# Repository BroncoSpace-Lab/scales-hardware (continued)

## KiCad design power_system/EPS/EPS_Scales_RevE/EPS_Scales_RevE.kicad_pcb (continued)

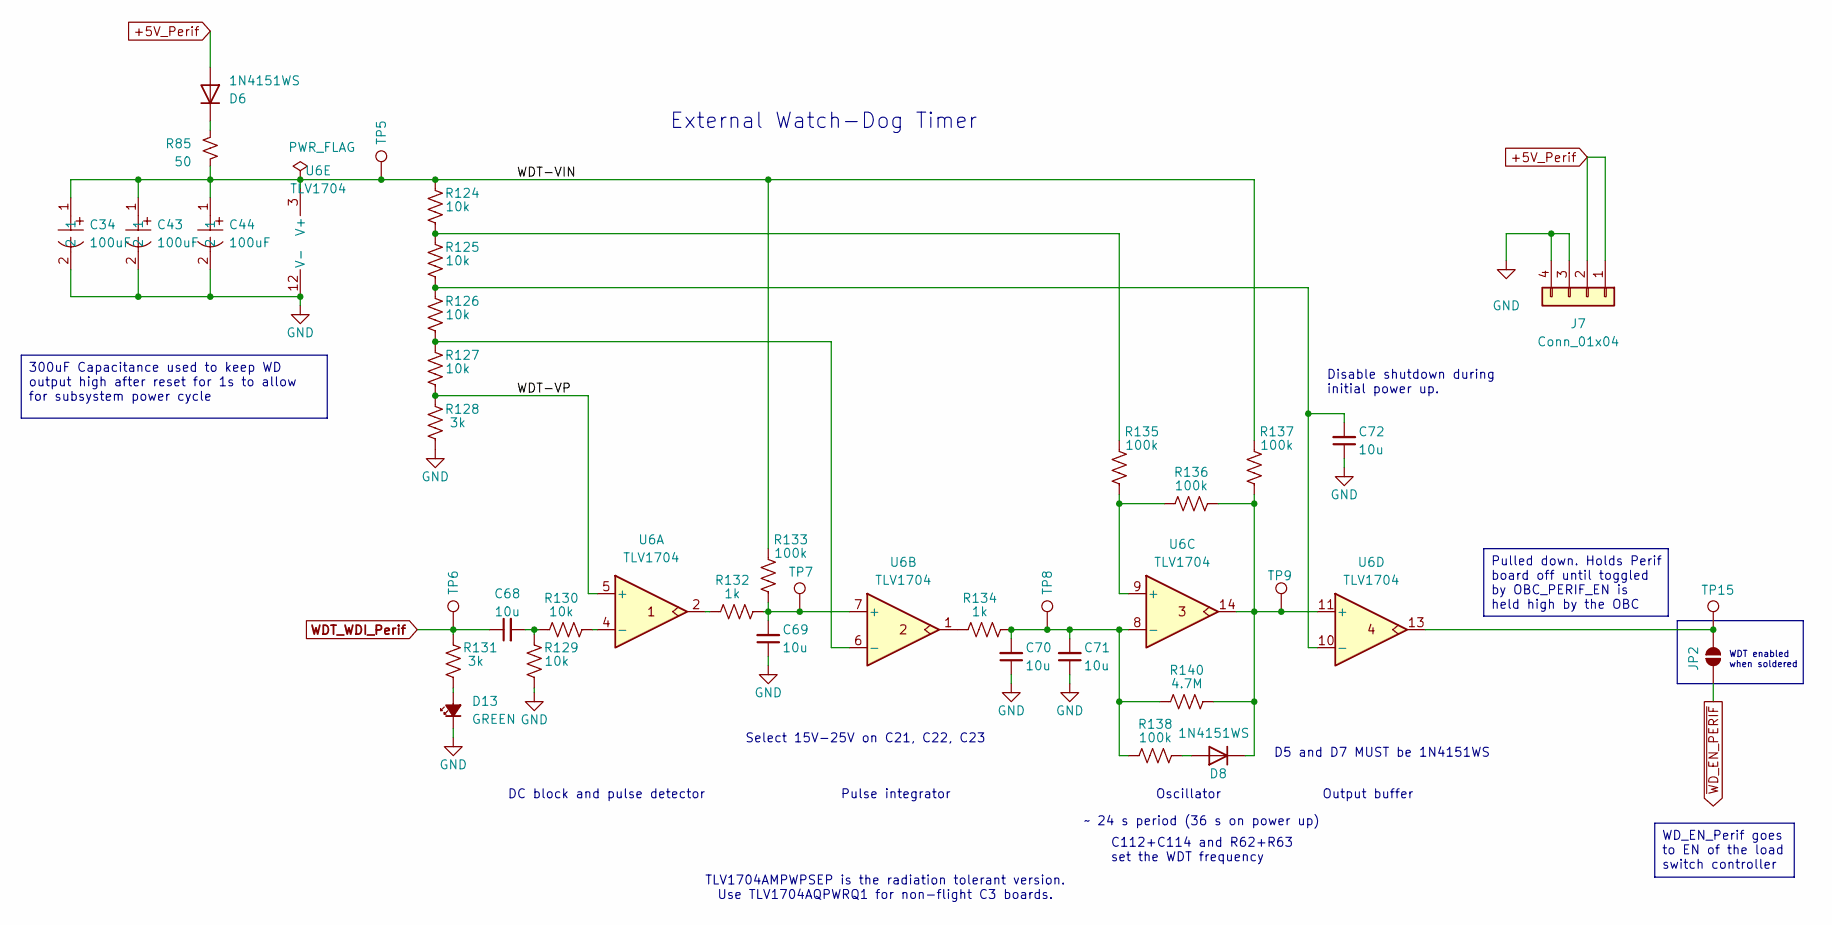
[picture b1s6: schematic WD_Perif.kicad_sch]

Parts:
C34, C43, C44: 100uF; CAP-SMD_L7.3-W6.1_TCN4227M025R0100; LCSC Part C2158793
C68, C69, C70, C71, C72: 10u; C0402; LCSC 194427
D6, D8: 1N4151WS; SOD2512X116N; MPN 1N4151WS-E3-08; LCSC C2979762
D13: GREEN; LED_0603_1608Metric; MPN 150060GS75000; LCSC C965799
J7: Conn_01x04; PinSocket_1x04_P2.54mm_Vertical
JP2: SolderJumper_2_Open; SolderJumper-2_P1.3mm_Open_RoundedPad1.0x1.5mm
R85: 50; R_1206_3216Metric; MPN ESR18EZPF10R0; LCSC C17903
R124, R125, R126, R127, R129, R130: 10k; R0402; LCSC C25531
R128, R131: 3k; R0402; LCSC C2909355
R132, R134: 1k; R0402; LCSC C106235
R133, R135, R136, R137, R138: 100k; R0402; LCSC C269673
R140: 4.7M; R0402; LCSC C474132
TP5, TP6, TP7, TP8, TP9, TP15: TestPoint; TestPoint_Pad_1.0x1.0mm
U6: TLV1704; TSSOP-14_4.4x5mm_P0.65mm; MPN TLV1704AQPWRQ1; LCSC C181596

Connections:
+5V_Perif: D6.2 (A), J7.1, J7.2; also elsewhere on the board
/Perif_Subsystem/WD_Perif/WDT-VIN: C34.1, C43.1, C44.1, R85.2, R124.2, R133.1, R137.1, TP5.1, U6.3 (V+)
/Perif_Subsystem/WD_Perif/WDT-VP: R127.1, R128.2, U6.5 (+)
GND: C34.2, C43.2, C44.2, C69.1, C70.1, C71.1, C72.1, D13.1 (K), J7.3, J7.4, R128.1, R129.1, U6.12 (V-); also elsewhere on the board
unnamed: C68.2, R129.2, R130.2
unnamed: D6.1 (C), R85.1
unnamed: D8.2 (A), R138.2
unnamed: D8.1 (C), R136.2, R137.2, R140.2, TP9.1, U6.11 (+), U6.14
unnamed: D13.2 (A), R131.1
unnamed: JP2.1 (A), TP15.1, U6.13
unnamed: R124.1, R125.2, R135.1
unnamed: R132.2, U6.2
unnamed: R134.2, U6.1
unnamed: R130.1, U6.4 (-)
unnamed: C69.2, R132.1, R133.2, TP7.1, U6.7 (+)
unnamed: R126.1, R127.2, U6.6 (-)
unnamed: R135.2, R136.1, U6.9 (+)
unnamed: C70.2, C71.2, R134.1, R138.1, R140.1, TP8.1, U6.8 (-)
unnamed: C72.2, R125.1, R126.2, U6.10 (-)
WDT_WDI_Perif: C68.1, R131.2, TP6.1; also elsewhere on the board
~WD_EN_PERIF: JP2.2 (B); also elsewhere on the board

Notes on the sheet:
External Watch-Dog Timer
Output buffer
TLV1704AMPWPSEP is the radiation tolerant version. Use TLV1704AQPWRQ1 for non-flight C3 boards.
~ 24 s period (36 s on power up)
Disable shutdown during initial power up.
DC block and pulse detector
WDT enabled when soldered
D5 and D7 MUST be 1N4151WS
Pulse integrator
Oscillator
C112+C114 and R62+R63 set the WDT frequency
Select 15V-25V on C21, C22, C23
WD_EN_Perif goes to EN of the load switch controller
300uF Capacitance used to keep WD output high after reset for 1s to allow for subsystem power cycle
Pulled down. Holds Perif board off until toggled by OBC_PERIF_EN is held high by the OBC

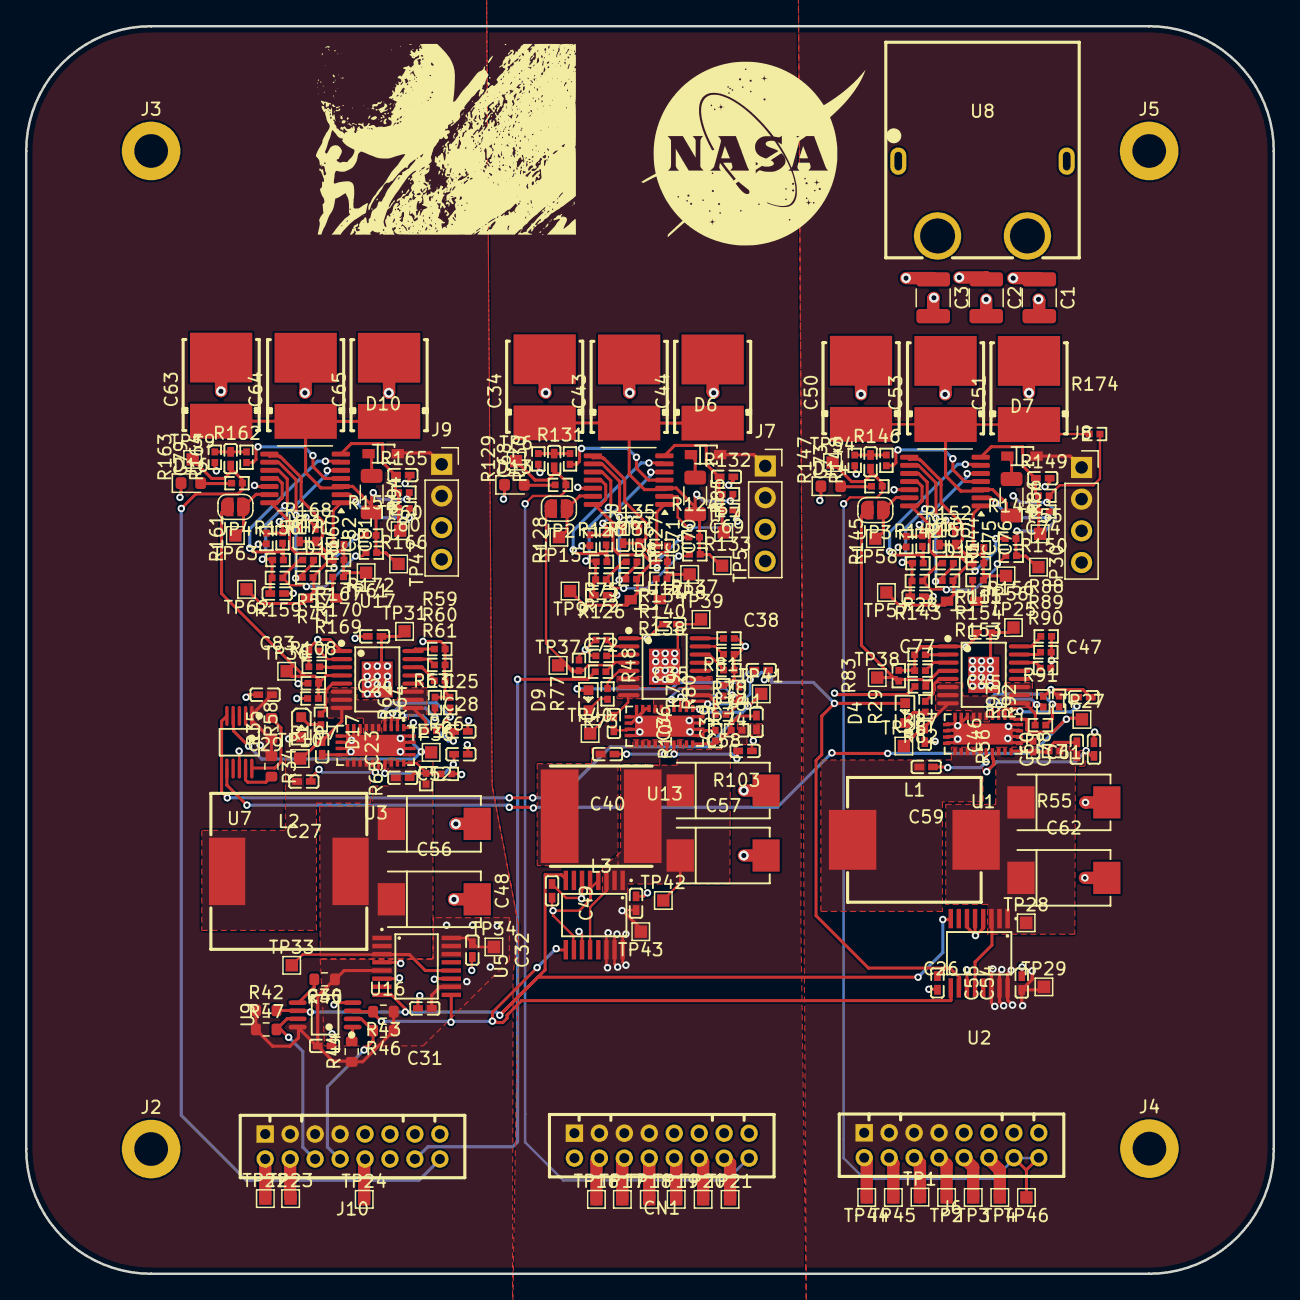
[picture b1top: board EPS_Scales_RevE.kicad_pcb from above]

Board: 4 copper layers, 100.0 x 100.0 mm, 253 parts (0 on the bottom side), 139 nets.

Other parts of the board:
C1, C2, C3: 10u; C_1210_3225Metric
J2, J3, J4, J5: Conn_01x01_Socket; MountingHole_2.7mm_M2.5_DIN965_Pad
U8: XT60PW-F_C428722; TH_2P-XT60PW-F

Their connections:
+V_Batt: C1.1, C2.1, C3.1, U8.3 (+); also elsewhere on the board
GND: C1.2, C2.2, C3.2, J2.1, J3.1, J4.1, J5.1, U8.1, U8.2, U8.4 (-); also elsewhere on the board

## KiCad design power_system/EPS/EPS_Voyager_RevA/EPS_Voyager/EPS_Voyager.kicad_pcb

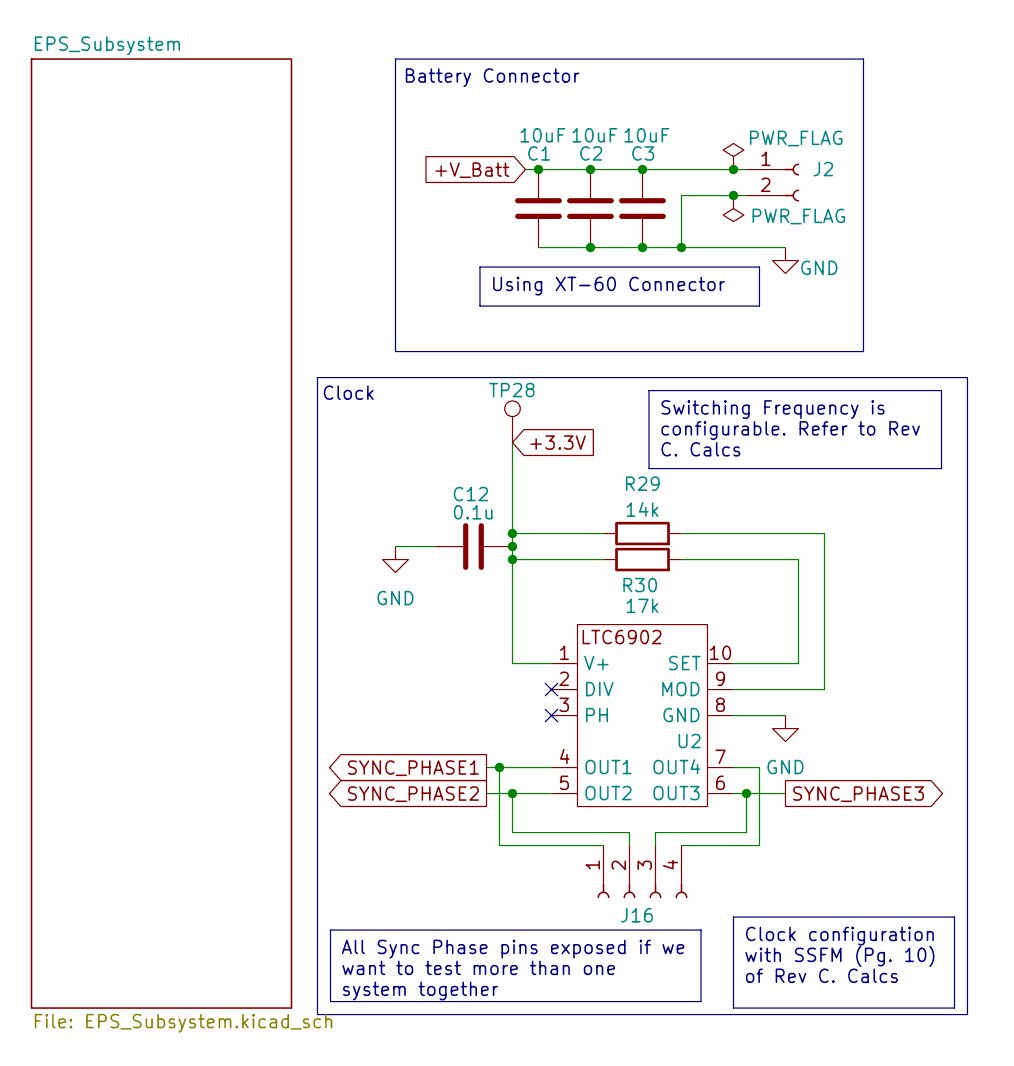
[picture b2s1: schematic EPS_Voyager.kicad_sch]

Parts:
C1, C2, C3: 10uF; C_1210_3225Metric
C12: 0.1u; C_1210_3225Metric
J2: Input Power; AMASS_XT60PW-F_1x02_P7.20mm_Horizontal
J16: Conn_01x04_Socket; PinSocket_1x04_P2.54mm_Vertical
R29: 14k
R30: 17k
TP28: TestPoint; TestPoint_Pad_1.0x1.0mm
U2: LTC6902

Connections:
+3.3V: C12.2, R29.1, R30.1, TP28.1, U2.1 (V+); also elsewhere on the board
+V_Batt: C1.1, C2.1, C3.1, J2.1; also elsewhere on the board
GND: C1.2, C2.2, C3.2, C12.1, J2.2, U2.8 (GND); also elsewhere on the board
unnamed 13: R29.2, U2.9 (MOD); also elsewhere on the board
unnamed 14: R30.2, U2.10 (SET); also elsewhere on the board
unnamed: J16.4, U2.7 (OUT4)
SYNC_PHASE1: J16.1, U2.4 (OUT1)
SYNC_PHASE2: J16.2, U2.5 (OUT2)
SYNC_PHASE3: J16.3, U2.6 (OUT3)

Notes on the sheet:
Clock
Battery Connector
Switching Frequency is configurable. Refer to Rev C. Calcs
Clock configuration with SSFM (Pg. 10) of Rev C. Calcs
Using XT-60 Connector
All Sync Phase pins exposed if we want to test more than one system together

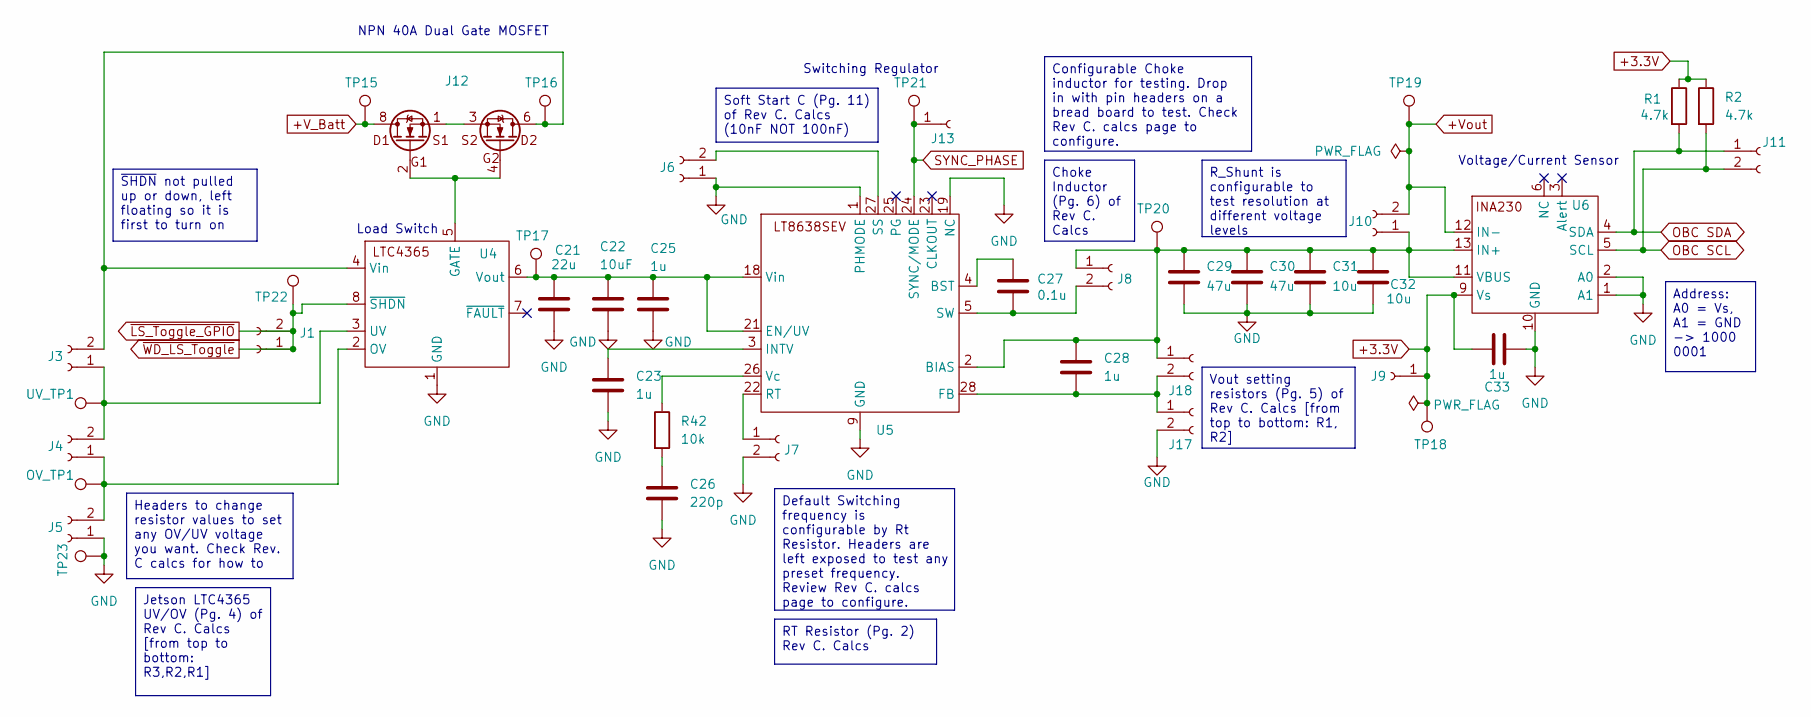
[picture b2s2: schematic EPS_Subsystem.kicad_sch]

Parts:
C21: 22u; C_1210_3225Metric
C22: 10uF; C_1210_3225Metric
C23, C25, C28, C33: 1u; C_1210_3225Metric
C26: 220p; C_1210_3225Metric
C27: 0.1u; C_1210_3225Metric
C29, C30: 47u; C_1210_3225Metric
C31, C32: 10u; C_1210_3225Metric
J1, J3, J4, J5, J6, J7, J8, J10, J11, J17, J18: Conn_01x02_Socket; PinSocket_1x02_P2.54mm_Vertical
J9, J13: Conn_01x01_Socket; PinSocket_1x01_P2.54mm_Vertical
J12: SISB46DN-T1-GE3
OV_TP1: TestPoint; TestPoint_Pad_1.0x1.0mm
R1, R2: 4.7k; R_0603_1608Metric
R42: 10k; R_0603_1608Metric
TP15, TP16, TP17, TP18, TP19, TP20, TP21, TP22, TP23: TestPoint; TestPoint_Pad_1.0x1.0mm
U4: LTC4365
U5: LT8638SEVPBF
U6: INA230; INA230AIRGTT
UV_TP1: TestPoint; TestPoint_Pad_1.0x1.0mm

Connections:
+3.3V: C33.2, J9.1, R1.1, R2.1, TP18.1, U6.9 (Vs); also elsewhere on the board
+V_Batt: J12.7, J12.8, TP15.1; also elsewhere on the board
+Vout: J10.2, TP19.1, U6.12 (IN-)
GND: C21.2, C22.2, C23.2, C25.2, C26.2, C29.2, C30.2, C31.2, C32.2, C33.1, J5.1, J6.1, J7.2, J17.2, TP23.1, U4.1 (GND), U5.1 (PHMODE), U5.9 (GND), U5.19 (NC), U6.1 (A1), U6.2 (A0), U6.10 (GND); also elsewhere on the board
unnamed: C26.1, R42.2
unnamed: J3.1, J4.2, U4.3 (UV), UV_TP1.1
unnamed: J3.2, J12.5, J12.6, TP16.1, U4.4 (Vin)
unnamed: J4.1, J5.2, OV_TP1.1, U4.2 (OV)
unnamed: J6.2, U5.27 (SS)
unnamed: J7.1, U5.22 (RT)
unnamed: C27.2, J8.2, U5.5 (SW)
unnamed: C28.1, C29.1, C30.1, C31.1, C32.1, J8.1, J10.1, J18.1, TP20.1, U5.2 (BIAS), U6.11 (VBUS), U6.13 (IN+)
unnamed: J12.1, J12.3
unnamed: C28.2, J17.1, J18.2, U5.28 (FB)
unnamed: J12.2, J12.4, U4.5 (GATE)
unnamed: C21.1, C22.1, C25.1, TP17.1, U4.6 (Vout), U5.18 (Vin), U5.21 (EN/UV)
unnamed: C27.1, U5.4 (BST)
unnamed: C23.1, U5.3 (INTV)
unnamed: R42.1, U5.26 (Vc)
OBC SCL: J11.2, R2.2, U6.5 (SCL)
OBC SDA: J11.1, R1.2, U6.4 (SDA)
SYNC_PHASE: J13.1, TP21.1, U5.24 (SYNC/MODE)
~LS_Toggle_GPIO: J1.1, J1.2, TP22.1, U4.8 (~SHDN)

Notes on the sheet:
Switching Regulator
NPN 40A Dual Gate MOSFET
Voltage/Current Sensor
Load Switch
RT Resistor (Pg. 2) Rev C. Calcs
Soft Start C (Pg. 11) of Rev C. Calcs (10nF NOT 100nF)
Headers to change resistor values to set any OV/UV voltage you want. Check Rev. C calcs for how to
R_Shunt is configurable to test resolution at different voltage levels
Configurable Choke inductor for testing. Drop in with pin headers on a bread board to test. Check Rev C. calcs page to configure.
Address: A0 = Vs, A1 = GND -> 1000 0001
Vout setting resistors (Pg. 5) of Rev C. Calcs [from top to bottom: R1, R2]
Choke Inductor (Pg. 6) of Rev C. Calcs
Jetson LTC4365 UV/OV (Pg. 4) of Rev C. Calcs [from top to bottom: R3,R2,R1]
~{SHDN} not pulled up or down, left floating so it is first to turn on
Default Switching frequency is configurable by Rt Resistor. Headers are left exposed to test any preset frequency. Review Rev C. calcs page to configure.

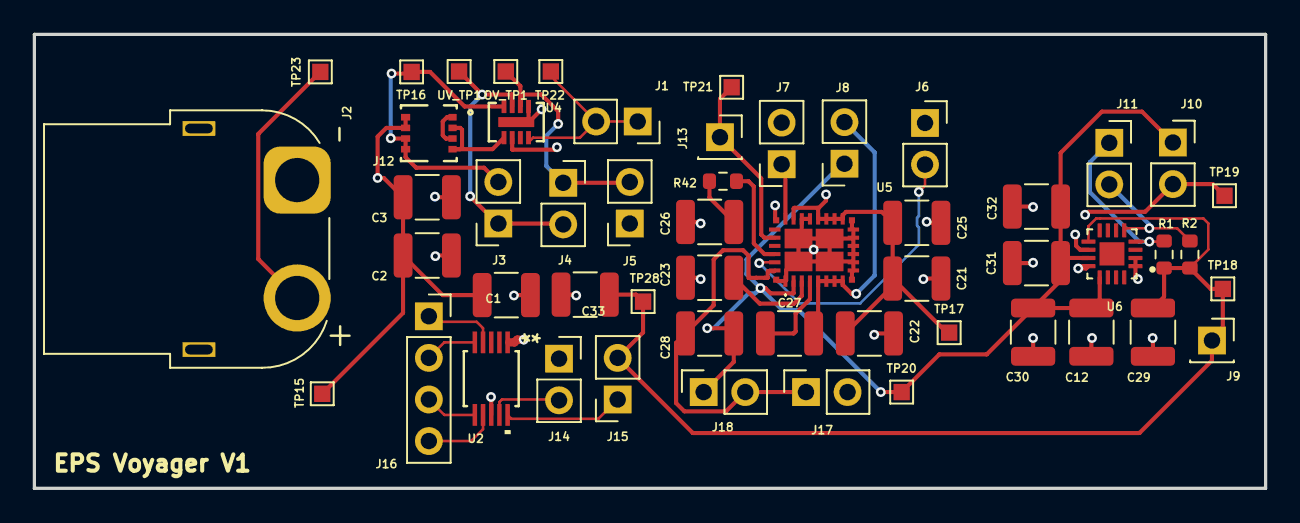
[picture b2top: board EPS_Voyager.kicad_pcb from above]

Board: 4 copper layers, 75.2 x 27.7 mm, 53 parts (0 on the bottom side), 29 nets.

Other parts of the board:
J14, J15: Conn_01x02_Socket; PinSocket_1x02_P2.54mm_Vertical

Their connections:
+3.3V: J14.1, J15.2; also elsewhere on the board
unnamed 13: J14.2; also elsewhere on the board
unnamed 14: J15.1; also elsewhere on the board

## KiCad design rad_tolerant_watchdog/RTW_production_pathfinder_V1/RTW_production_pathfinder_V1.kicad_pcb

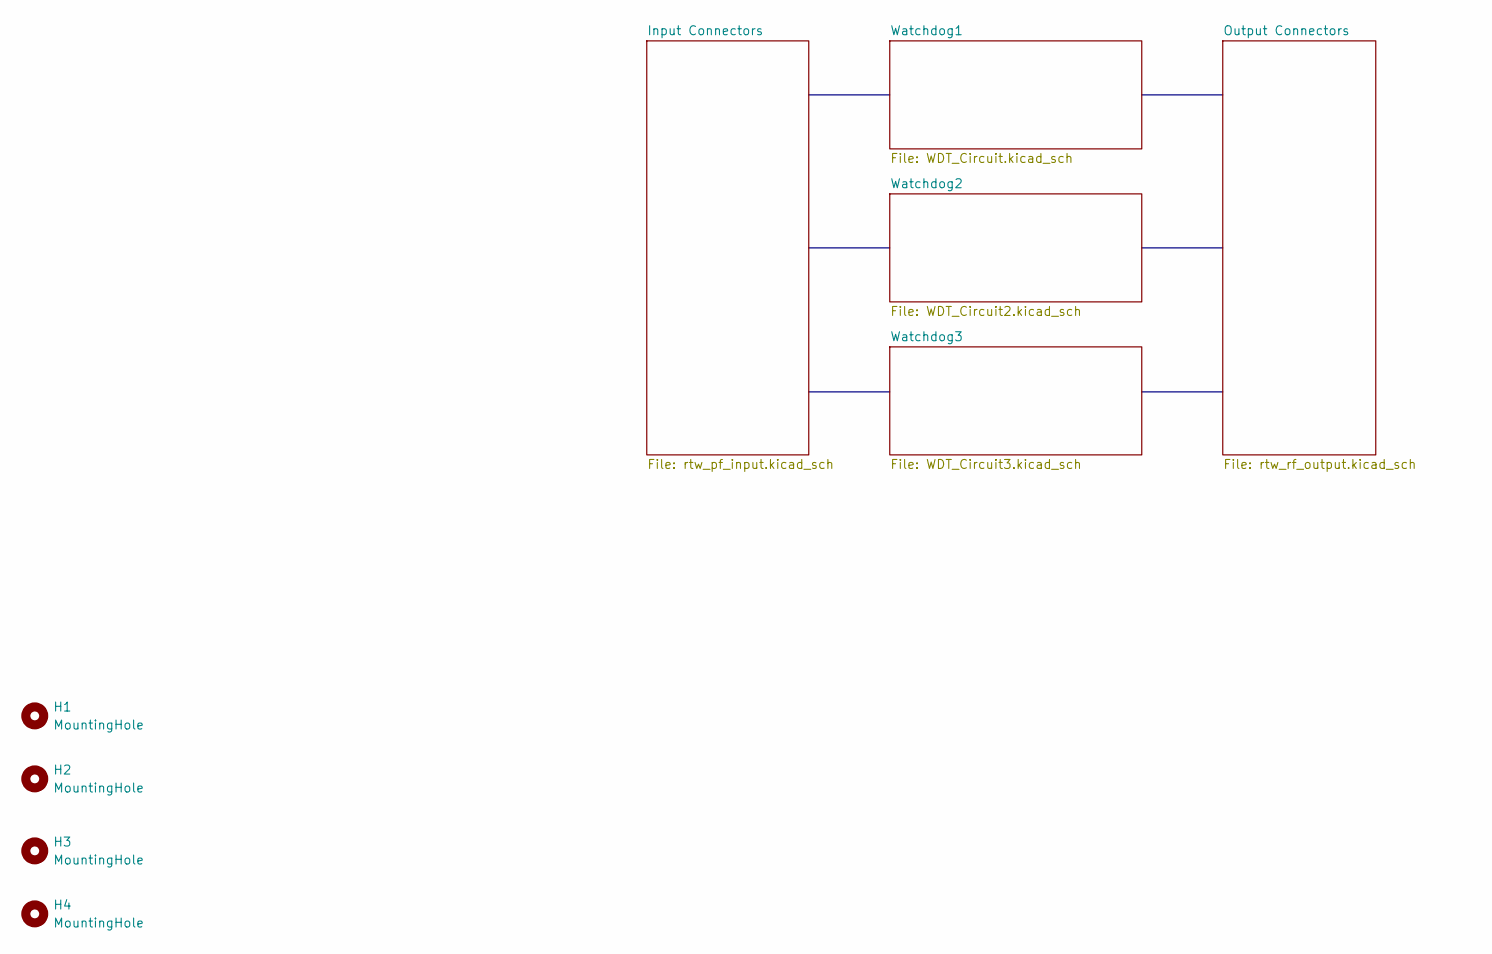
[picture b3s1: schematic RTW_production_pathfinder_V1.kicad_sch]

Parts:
H1, H2, H3, H4: MountingHole; MountingHole_2.2mm_M2_DIN965_Pad

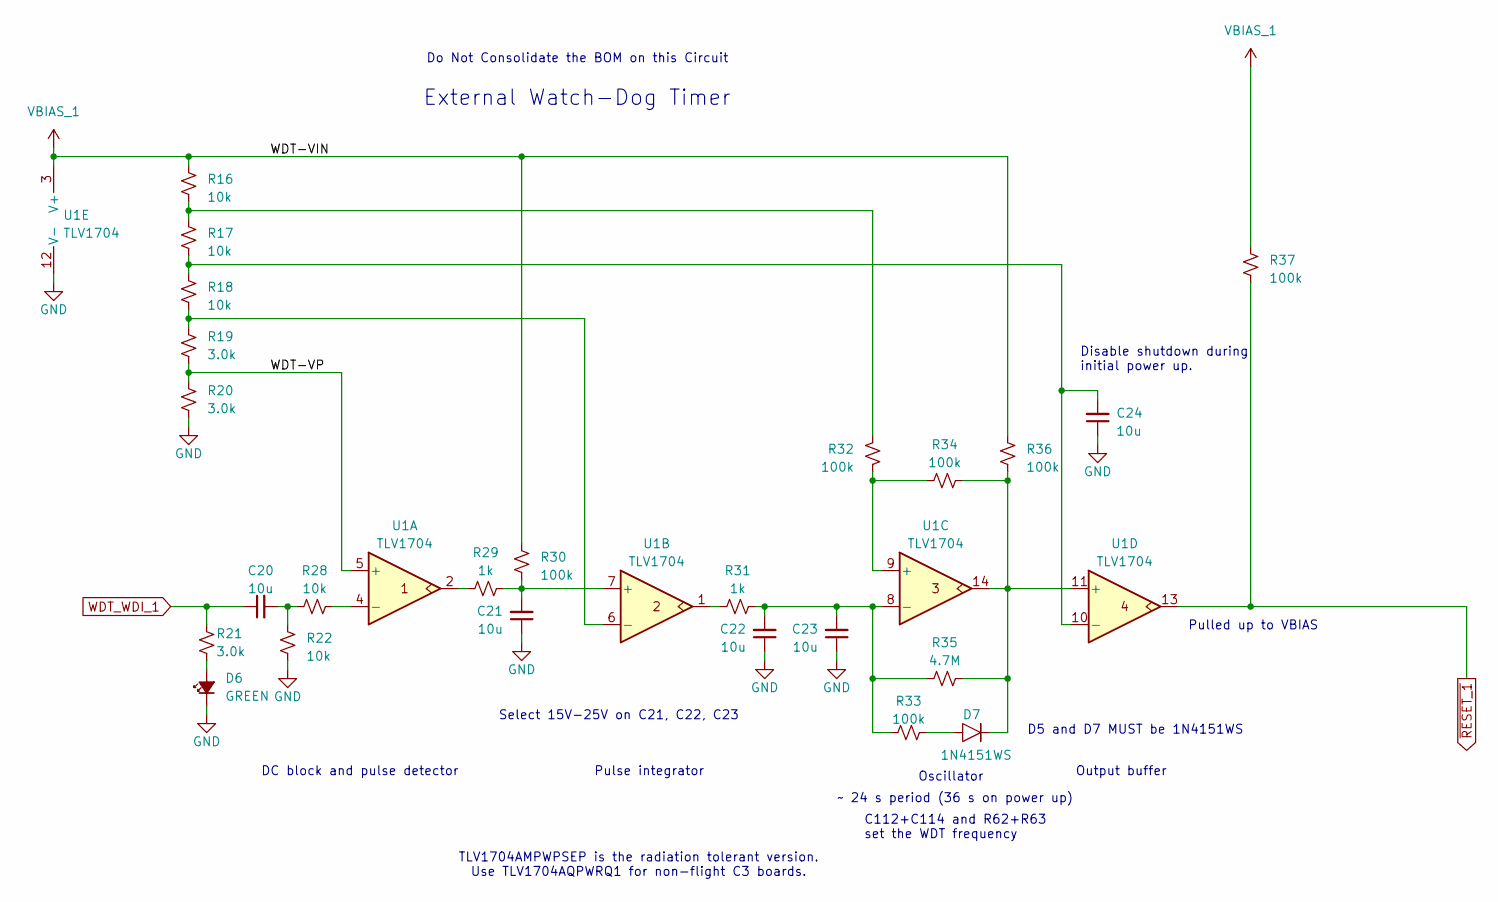
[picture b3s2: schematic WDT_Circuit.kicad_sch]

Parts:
C20, C21, C22, C23, C24: 10u; C_0603_1608Metric; MPN GRT188R61C106KE13D
D6: GREEN; LED_0603_1608Metric; MPN 150060GS75000
D7: 1N4151WS; D_SOD-323; MPN 1N4151WS-E3-08
R16, R17, R18, R22, R28: 10k; R_0603_1608Metric; MPN RMCF0603FT10K0
R19, R20, R21: 3.0k; R_0603_1608Metric; MPN RMCF0603FT3K00
R29, R31: 1k; R_0603_1608Metric; MPN RMCF0603FT1K00
R30, R32, R33, R34, R36, R37: 100k; R_0603_1608Metric; MPN RMCF0603FT100K
R35: 4.7M; R_0603_1608Metric; MPN RMCF0603FT4M70
U1: TLV1704; TSSOP-14_4.4x5mm_P0.65mm; MPN TLV1704AQPWRQ1

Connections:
/Watchdog1/WDT-VP: R19.2, R20.1, U1.5 (+)
GND: C21.1, C22.1, C23.1, C24.1, D6.1 (K), R20.2, R22.2, U1.12 (V-); also elsewhere on the board
unnamed: C20.2, R22.1, R28.1
unnamed: D6.2 (A), R21.2
unnamed: D7.2, R33.1
unnamed: R16.2, R17.1, R32.2
unnamed: R29.1, U1.2
unnamed: R31.1, U1.1
unnamed: R28.2, U1.4 (-)
unnamed: C21.2, R29.2, R30.2, U1.7 (+)
unnamed: R18.2, R19.1, U1.6 (-)
unnamed: R32.1, R34.1, U1.9 (+)
unnamed: C22.2, C23.2, R31.2, R33.2, R35.2, U1.8 (-)
unnamed: D7.1, R34.2, R35.1, R36.1, U1.11 (+), U1.14
unnamed: C24.2, R17.2, R18.1, U1.10 (-)
VBIAS_1: R16.1, R30.1, R36.2, R37.2, U1.3 (V+); also elsewhere on the board
WDT_WDI_1: C20.1, R21.1; also elsewhere on the board
~RESET_1: R37.1, U1.13; also elsewhere on the board

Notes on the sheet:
Pulled up to VBIAS
TLV1704AMPWPSEP is the radiation tolerant version. Use TLV1704AQPWRQ1 for non-flight C3 boards.
~ 24 s period (36 s on power up)
Do Not Consolidate the BOM on this Circuit
Select 15V-25V on C21, C22, C23
Disable shutdown during initial power up.
Pulse integrator
External Watch-Dog Timer
DC block and pulse detector
D5 and D7 MUST be 1N4151WS
Oscillator
Output buffer
C112+C114 and R62+R63 set the WDT frequency

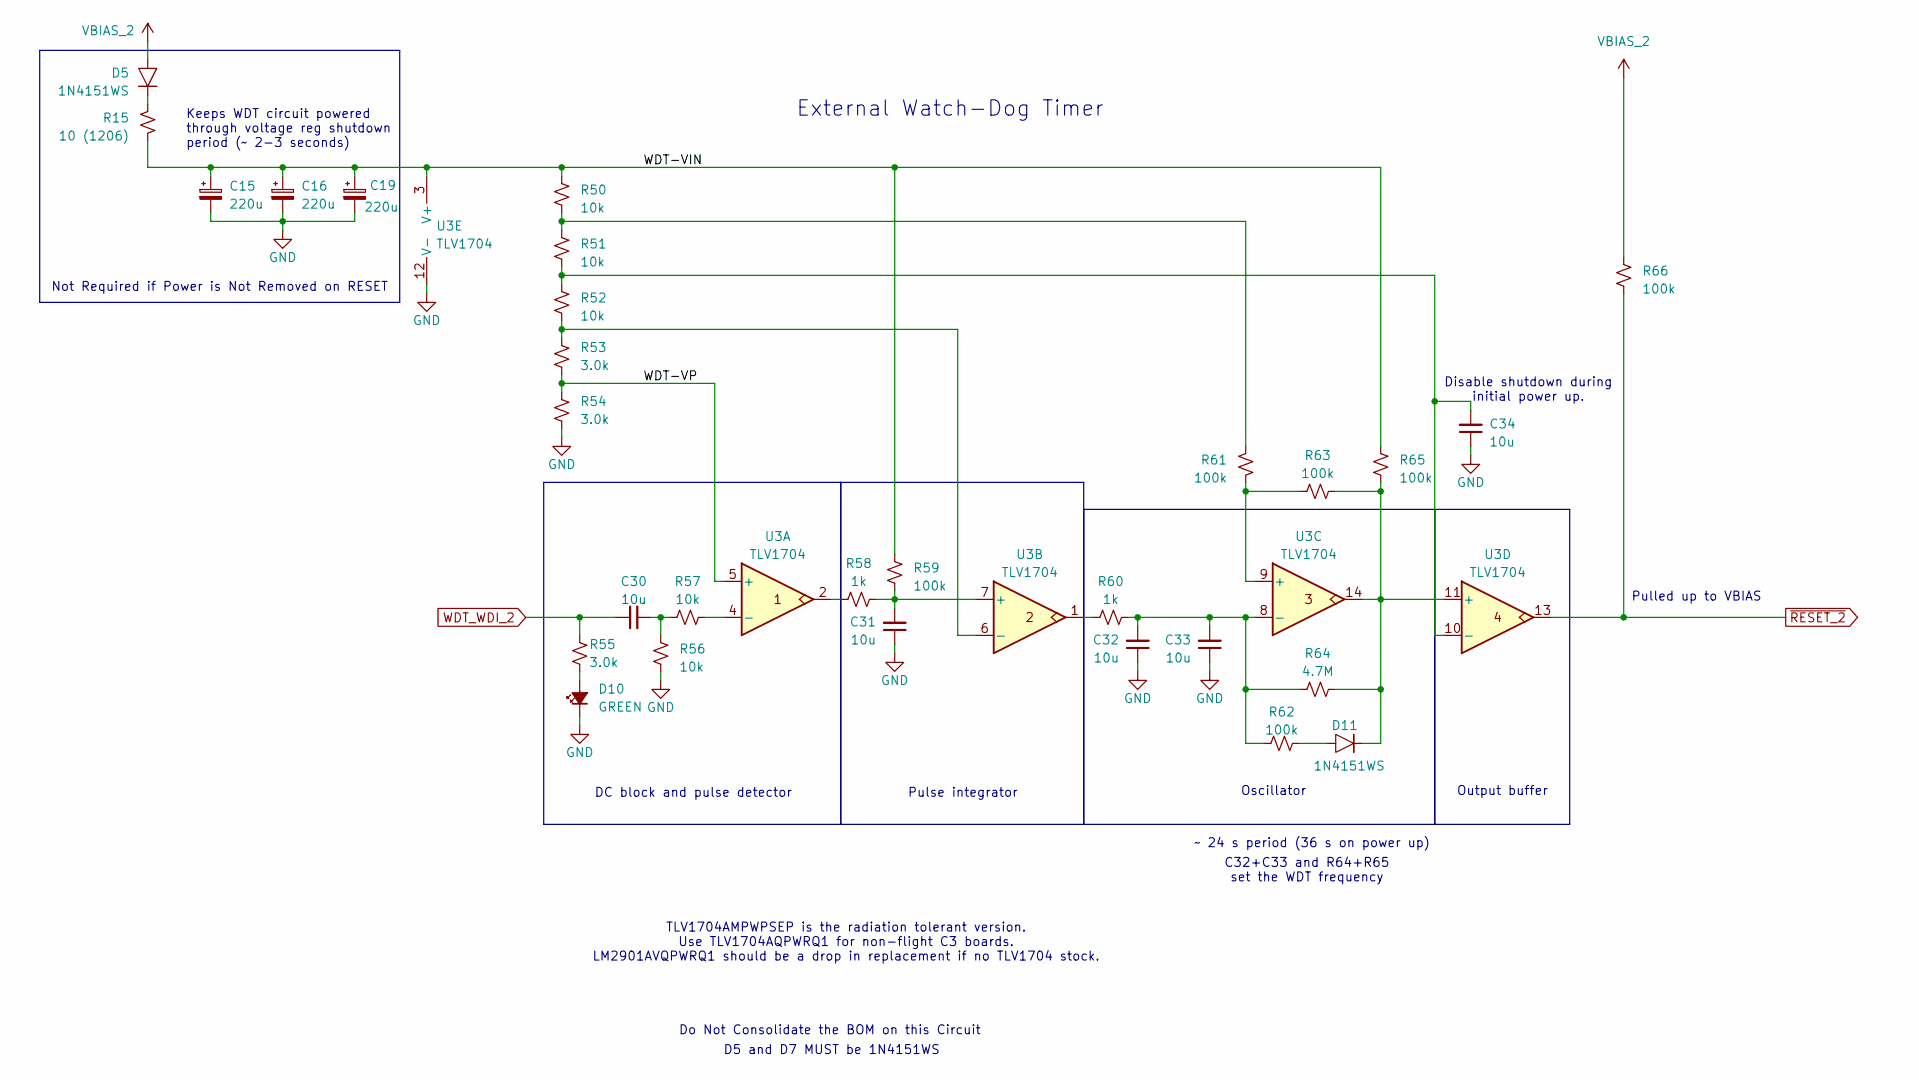
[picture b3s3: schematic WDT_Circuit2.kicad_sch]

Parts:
C15, C16, C19: 220u; CP_EIA-7361-38_AVX-V; MPN TCN4227M025R0100
C30, C31, C32, C33, C34: 10u; C_0603_1608Metric; MPN GRT188R61C106KE13D
D5, D11: 1N4151WS; D_SOD-323; MPN 1N4151WS-E3-08
D10: GREEN; LED_0603_1608Metric; MPN 150060GS75000
R15: 10 (1206); R_1206_3216Metric; MPN ESR18EZPF10R0
R50, R51, R52, R56, R57: 10k; R_0603_1608Metric; MPN RMCF0603FT10K0
R53, R54, R55: 3.0k; R_0603_1608Metric; MPN RMCF0603FT3K00
R58, R60: 1k; R_0603_1608Metric; MPN RMCF0603FT1K00
R59, R61, R62, R63, R65, R66: 100k; R_0603_1608Metric; MPN RMCF0603FT100K
R64: 4.7M; R_0603_1608Metric; MPN RMCF0603FT4M70
U3: TLV1704; TSSOP-14_4.4x5mm_P0.65mm; MPN TLV1704AQPWRQ1

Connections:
/Watchdog2/WDT-VIN: C15.1, C16.1, C19.1, R15.2, R50.1, R59.1, R65.2, U3.3 (V+)
/Watchdog2/WDT-VP: R53.2, R54.1, U3.5 (+)
GND: C15.2, C16.2, C19.2, C31.1, C32.1, C33.1, C34.1, D10.1 (K), R54.2, R56.2, U3.12 (V-); also elsewhere on the board
unnamed: C30.2, R56.1, R57.1
unnamed: D5.1, R15.1
unnamed: D10.2 (A), R55.2
unnamed: D11.2, R62.1
unnamed: R50.2, R51.1, R61.2
unnamed: R58.1, U3.2
unnamed: R60.1, U3.1
unnamed: R57.2, U3.4 (-)
unnamed: C31.2, R58.2, R59.2, U3.7 (+)
unnamed: R52.2, R53.1, U3.6 (-)
unnamed: R61.1, R63.1, U3.9 (+)
unnamed: C32.2, C33.2, R60.2, R62.2, R64.2, U3.8 (-)
unnamed: D11.1, R63.2, R64.1, R65.1, U3.11 (+), U3.14
unnamed: C34.2, R51.2, R52.1, U3.10 (-)
VBIAS_2: D5.2, R66.2; also elsewhere on the board
WDT_WDI_2: C30.1, R55.1; also elsewhere on the board
~RESET_2: R66.1, U3.13; also elsewhere on the board

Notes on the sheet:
Not Required if Power is Not Removed on RESET
Pulled up to VBIAS
TLV1704AMPWPSEP is the radiation tolerant version. Use TLV1704AQPWRQ1 for non-flight C3 boards. LM2901AVQPWRQ1 should be a drop in replacement if no TLV1704 stock.
~ 24 s period (36 s on power up)
Do Not Consolidate the BOM on this Circuit
Disable shutdown during initial power up.
Pulse integrator
External Watch-Dog Timer
Keeps WDT circuit powered through voltage reg shutdown period (~ 2-3 seconds)
DC block and pulse detector
D5 and D7 MUST be 1N4151WS
Oscillator
Output buffer
C32+C33 and R64+R65 set the WDT frequency

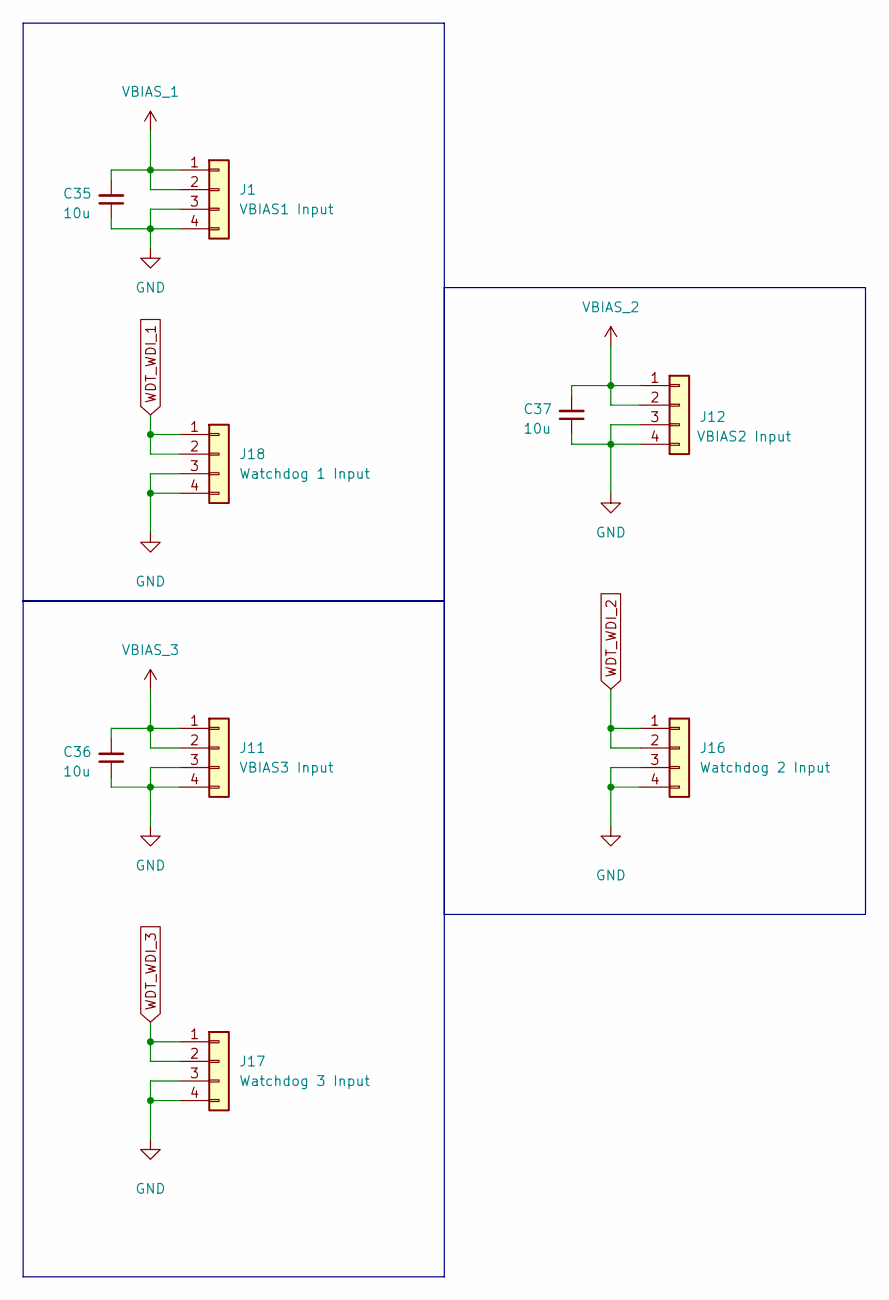
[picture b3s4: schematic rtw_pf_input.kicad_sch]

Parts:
C35, C36, C37: 10u; C_0603_1608Metric; MPN GRT188R61C106KE13D
J1: VBIAS1 Input; PinHeader_1x04_P2.54mm_Vertical
J11: VBIAS3 Input; PinHeader_1x04_P2.54mm_Vertical
J12: VBIAS2 Input; PinHeader_1x04_P2.54mm_Vertical
J16: Watchdog 2 Input; PinHeader_1x04_P2.54mm_Vertical
J17: Watchdog 3 Input; PinHeader_1x04_P2.54mm_Vertical
J18: Watchdog 1 Input; PinHeader_1x04_P2.54mm_Vertical

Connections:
GND: C35.1, C36.1, C37.1, J1.3, J1.4, J11.3, J11.4, J12.3, J12.4, J16.3, J16.4, J17.3, J17.4, J18.3, J18.4; also elsewhere on the board
VBIAS_1: C35.2, J1.1, J1.2; also elsewhere on the board
VBIAS_2: C37.2, J12.1, J12.2; also elsewhere on the board
VBIAS_3: C36.2, J11.1, J11.2; also elsewhere on the board
WDT_WDI_1: J18.1, J18.2; also elsewhere on the board
WDT_WDI_2: J16.1, J16.2; also elsewhere on the board
WDT_WDI_3: J17.1, J17.2; also elsewhere on the board

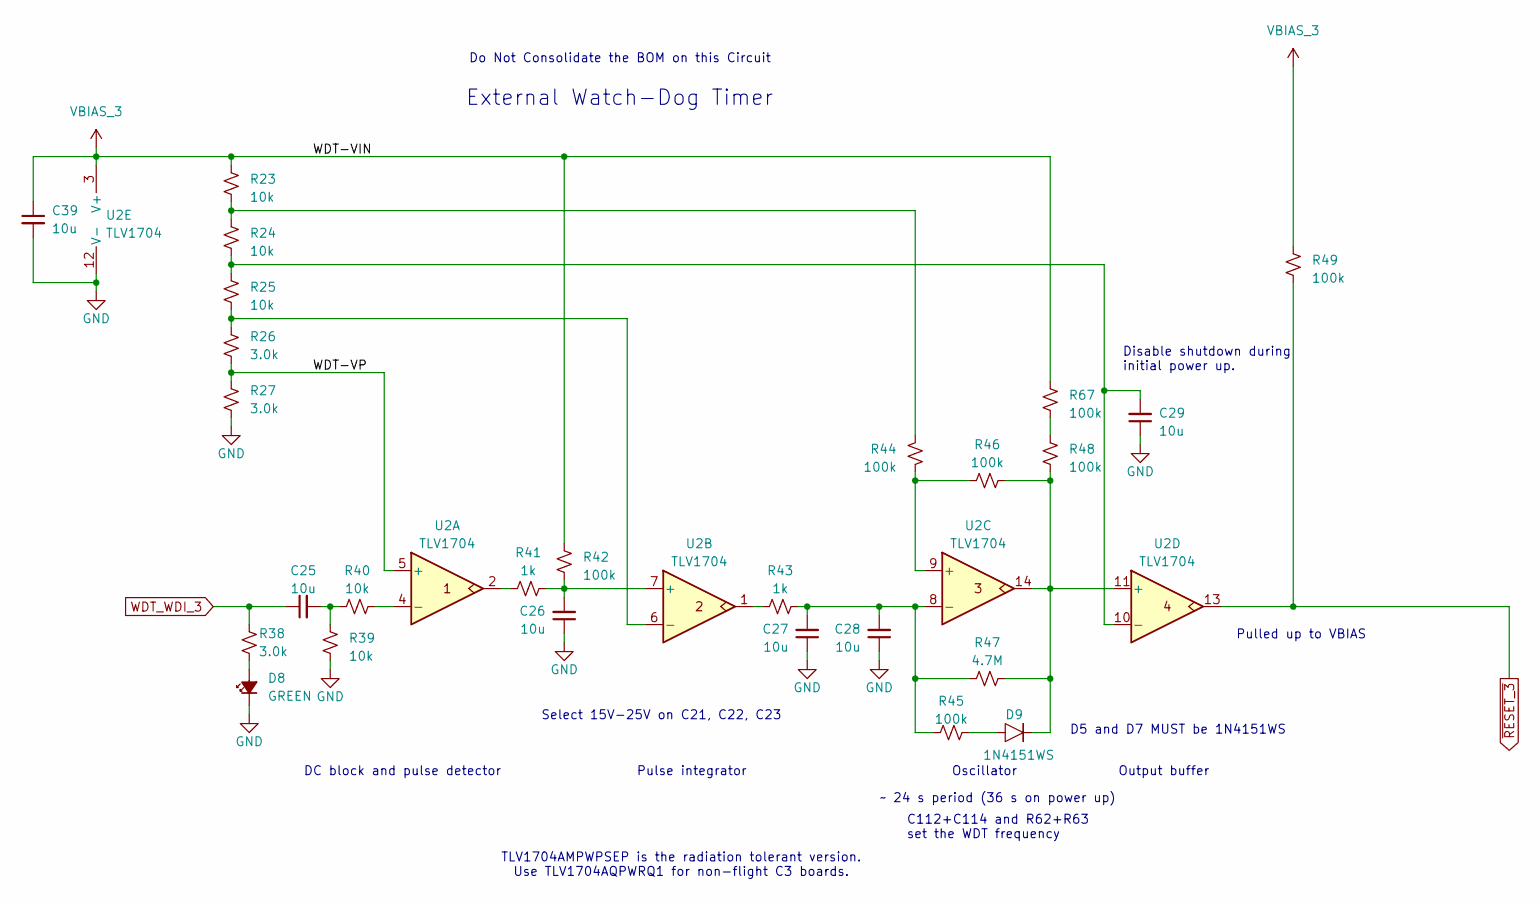
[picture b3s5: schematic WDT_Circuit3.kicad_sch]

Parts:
C25, C26, C27, C28, C29, C39: 10u; C_0603_1608Metric; MPN GRT188R61C106KE13D
D8: GREEN; LED_0603_1608Metric; MPN 150060GS75000
D9: 1N4151WS; D_SOD-323; MPN 1N4151WS-E3-08
R23, R24, R25, R39, R40: 10k; R_0603_1608Metric; MPN RMCF0603FT10K0
R26, R27, R38: 3.0k; R_0603_1608Metric; MPN RMCF0603FT3K00
R41, R43: 1k; R_0603_1608Metric; MPN RMCF0603FT1K00
R42, R44, R45, R46, R48, R49, R67: 100k; R_0603_1608Metric; MPN RMCF0603FT100K
R47: 4.7M; R_0603_1608Metric; MPN RMCF0603FT4M70
U2: TLV1704; TSSOP-14_4.4x5mm_P0.65mm; MPN TLV1704AQPWRQ1

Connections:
/Watchdog3/WDT-VP: R26.2, R27.1, U2.5 (+)
GND: C26.1, C27.1, C28.1, C29.1, C39.2, D8.1 (K), R27.2, R39.2, U2.12 (V-); also elsewhere on the board
unnamed: C25.2, R39.1, R40.1
unnamed: D8.2 (A), R38.2
unnamed: D9.2, R45.1
unnamed: R23.2, R24.1, R44.2
unnamed: R41.1, U2.2
unnamed: R43.1, U2.1
unnamed: R48.2, R67.1
unnamed: R40.2, U2.4 (-)
unnamed: C26.2, R41.2, R42.2, U2.7 (+)
unnamed: R25.2, R26.1, U2.6 (-)
unnamed: R44.1, R46.1, U2.9 (+)
unnamed: C27.2, C28.2, R43.2, R45.2, R47.2, U2.8 (-)
unnamed: D9.1, R46.2, R47.1, R48.1, U2.11 (+), U2.14
unnamed: C29.2, R24.2, R25.1, U2.10 (-)
VBIAS_3: C39.1, R23.1, R42.1, R49.2, R67.2, U2.3 (V+); also elsewhere on the board
WDT_WDI_3: C25.1, R38.1; also elsewhere on the board
~RESET_3: R49.1, U2.13; also elsewhere on the board

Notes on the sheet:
TLV1704AMPWPSEP is the radiation tolerant version. Use TLV1704AQPWRQ1 for non-flight C3 boards.
~ 24 s period (36 s on power up)
Do Not Consolidate the BOM on this Circuit
Select 15V-25V on C21, C22, C23
Disable shutdown during initial power up.
Pulse integrator
External Watch-Dog Timer
DC block and pulse detector
D5 and D7 MUST be 1N4151WS
Oscillator
Output buffer
C112+C114 and R62+R63 set the WDT frequency
Pulled up to VBIAS

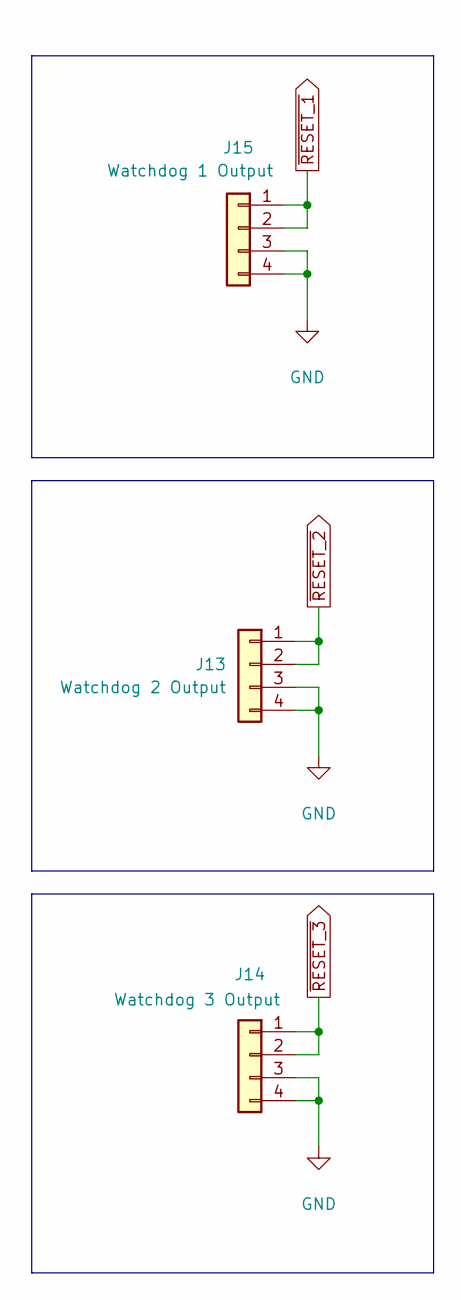
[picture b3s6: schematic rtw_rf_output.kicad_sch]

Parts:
J13: Watchdog 2 Output; PinHeader_1x04_P2.54mm_Vertical
J14: Watchdog 3 Output; PinHeader_1x04_P2.54mm_Vertical
J15: Watchdog 1 Output; PinHeader_1x04_P2.54mm_Vertical

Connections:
GND: J13.3, J13.4, J14.3, J14.4, J15.3, J15.4; also elsewhere on the board
~RESET_1: J15.1, J15.2; also elsewhere on the board
~RESET_2: J13.1, J13.2; also elsewhere on the board
~RESET_3: J14.1, J14.2; also elsewhere on the board
